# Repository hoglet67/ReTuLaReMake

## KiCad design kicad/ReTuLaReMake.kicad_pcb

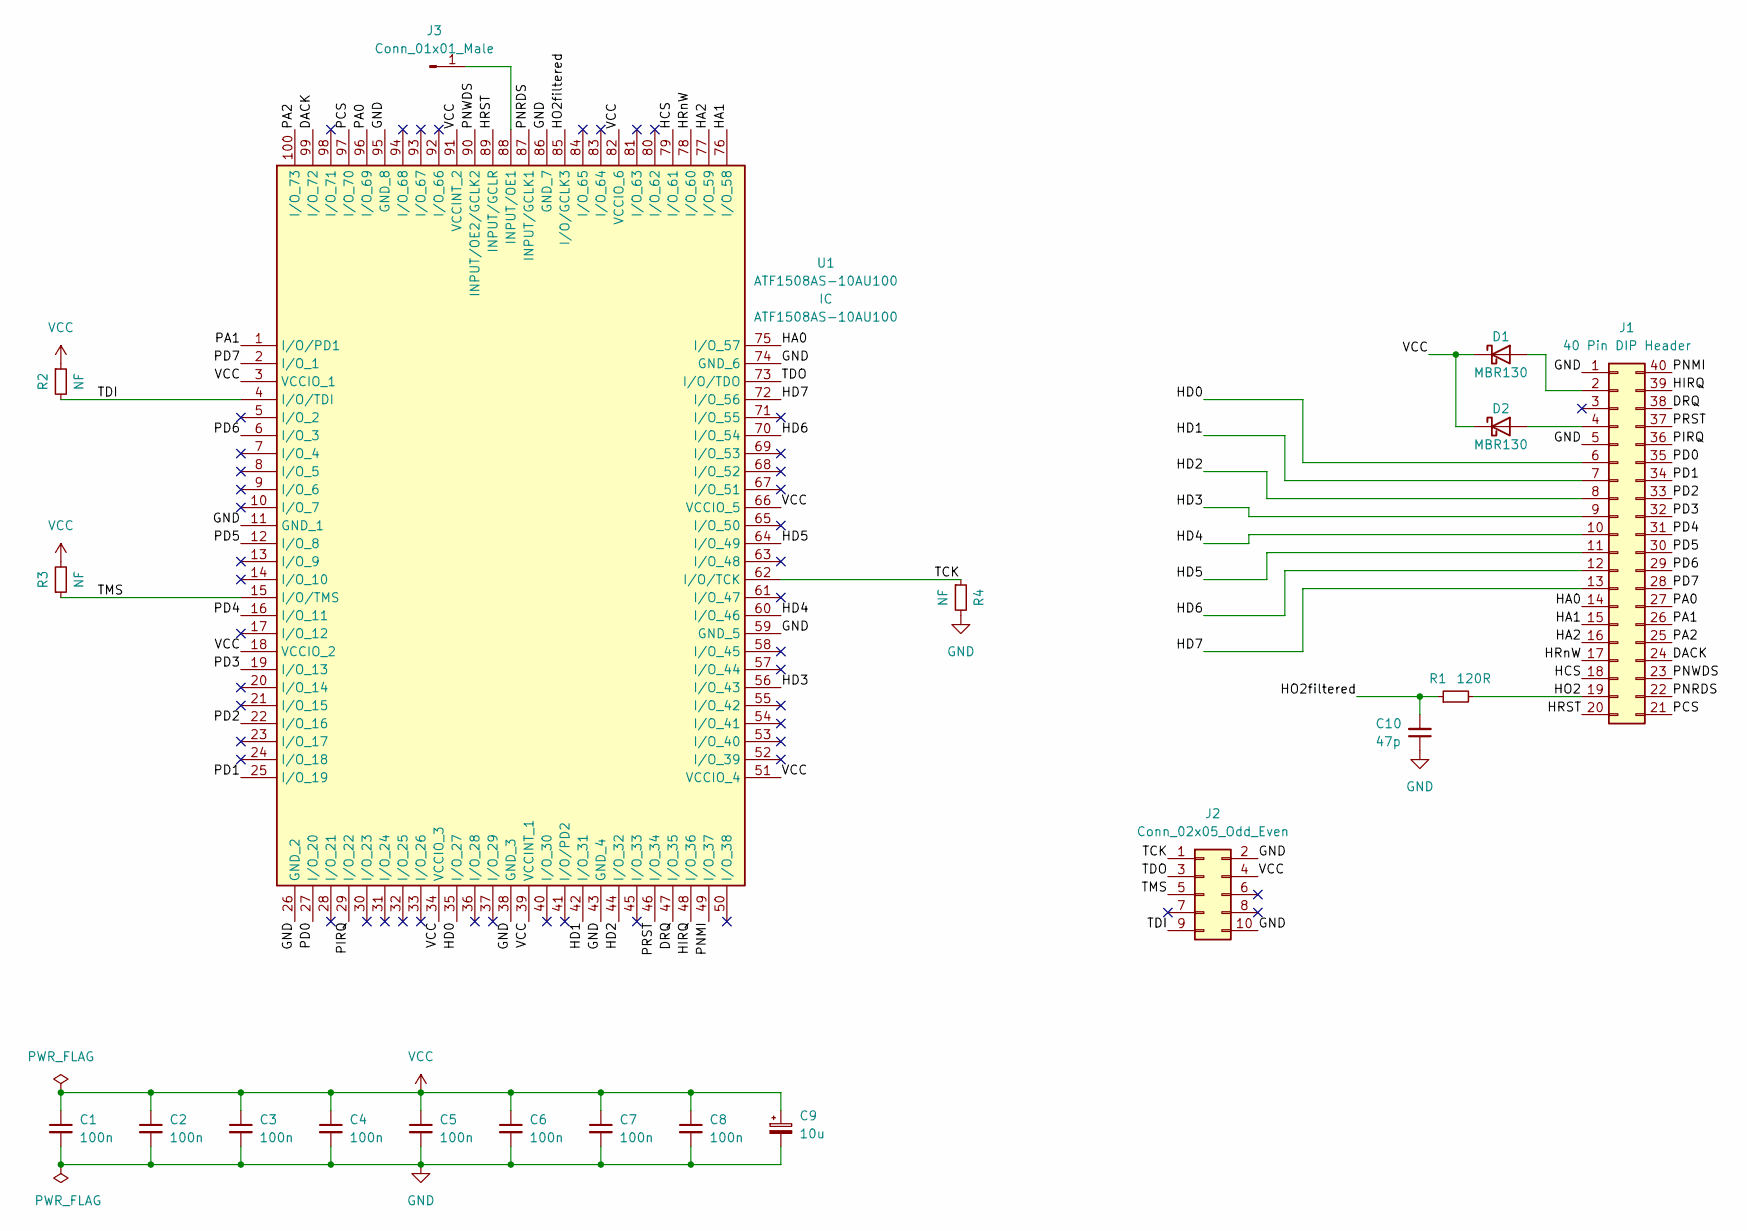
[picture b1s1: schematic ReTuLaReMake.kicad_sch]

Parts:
C1, C2, C3, C4, C5, C6, C7, C8: 100n; C_0805_2012Metric_Pad1.18x1.45mm_HandSolder
C9: 10u; CP_EIA-6032-28_Kemet-C_Pad2.25x2.35mm_HandSolder
C10: 47p; C_0805_2012Metric_Pad1.18x1.45mm_HandSolder
D1, D2: MBR130; D_SOD-123
J1: 40 Pin DIP Header; DIP-40_W15.24mm_Header
J2: Conn_02x05_Odd_Even; PinHeader_2x05_P2.54mm_Vertical
J3: Conn_01x01_Male; PinHeader_1x01_P2.54mm_Vertical
R1: 120R; R_0805_2012Metric_Pad1.20x1.40mm_HandSolder
R2, R3, R4: NF; R_0805_2012Metric_Pad1.20x1.40mm_HandSolder
U1: ATF1508AS-10AU100; TQFP-100_14x14mm_P0.5mm; Manufacturer_Part_Number ATF1508AS-10AU100; Mouser Part Number 556-AF1508AS10AU100

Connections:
/DACK: J1.24, U1.99 (I/O_72)
/DRQ: J1.38, U1.47 (I/O_35)
/HA0: J1.14, U1.75 (I/O_57)
/HA1: J1.15, U1.76 (I/O_58)
/HA2: J1.16, U1.77 (I/O_59)
/HCS: J1.18, U1.79 (I/O_61)
/HD0: J1.6, U1.35 (I/O_27)
/HD1: J1.7, U1.42 (I/O_31)
/HD2: J1.8, U1.44 (I/O_32)
/HD3: J1.9, U1.56 (I/O_43)
/HD4: J1.10, U1.60 (I/O_46)
/HD5: J1.11, U1.64 (I/O_49)
/HD6: J1.12, U1.70 (I/O_54)
/HD7: J1.13, U1.72 (I/O_56)
/HIRQ: J1.39, U1.48 (I/O_36)
/HO2: J1.19, R1.2
/HO2filtered: C10.2, R1.1, U1.85 (I/O/GCLK3)
/HRST: J1.20, U1.89 (INPUT/GCLR)
/HRnW: J1.17, U1.78 (I/O_60)
/PA0: J1.27, U1.96 (I/O_69)
/PA1: J1.26, U1.1 (I/O/PD1)
/PA2: J1.25, U1.100 (I/O_73)
/PCS: J1.21, U1.97 (I/O_70)
/PD0: J1.35, U1.27 (I/O_20)
/PD1: J1.34, U1.25 (I/O_19)
/PD2: J1.33, U1.22 (I/O_16)
/PD3: J1.32, U1.19 (I/O_13)
/PD4: J1.31, U1.16 (I/O_11)
/PD5: J1.30, U1.12 (I/O_8)
/PD6: J1.29, U1.6 (I/O_3)
/PD7: J1.28, U1.2 (I/O_1)
/PIRQ: J1.36, U1.29 (I/O_22)
/PNMI: J1.40, U1.49 (I/O_37)
/PNRDS: J1.22, U1.87 (INPUT/GCLK1)
/PNWDS: J1.23, U1.90 (INPUT/OE2/GCLK2)
/PRST: J1.37, U1.46 (I/O_34)
/TCK: J2.1, R4.1, U1.62 (I/O/TCK)
/TDI: J2.9, R2.2, U1.4 (I/O/TDI)
/TDO: J2.3, U1.73 (I/O/TDO)
/TMS: J2.5, R3.1, U1.15 (I/O/TMS)
GND: C1.2, C2.2, C3.2, C4.2, C5.2, C6.2, C7.2, C8.2, C9.2, C10.1, J1.1, J1.5, J2.2, J2.10, R4.2, U1.11 (GND_1), U1.26 (GND_2), U1.38 (GND_3), U1.43 (GND_4), U1.59 (GND_5), U1.74 (GND_6), U1.86 (GND_7), U1.95 (GND_8)
unnamed: D1.2 (A), J1.2
unnamed: D2.2 (A), J1.4
unnamed: J3.1, U1.88 (INPUT/OE1)
VCC: C1.1, C2.1, C3.1, C4.1, C5.1, C6.1, C7.1, C8.1, C9.1, D1.1 (K), D2.1 (K), J2.4, R2.1, R3.2, U1.3 (VCCIO_1), U1.18 (VCCIO_2), U1.34 (VCCIO_3), U1.39 (VCCINT_1), U1.51 (VCCIO_4), U1.66 (VCCIO_5), U1.82 (VCCIO_6), U1.91 (VCCINT_2)

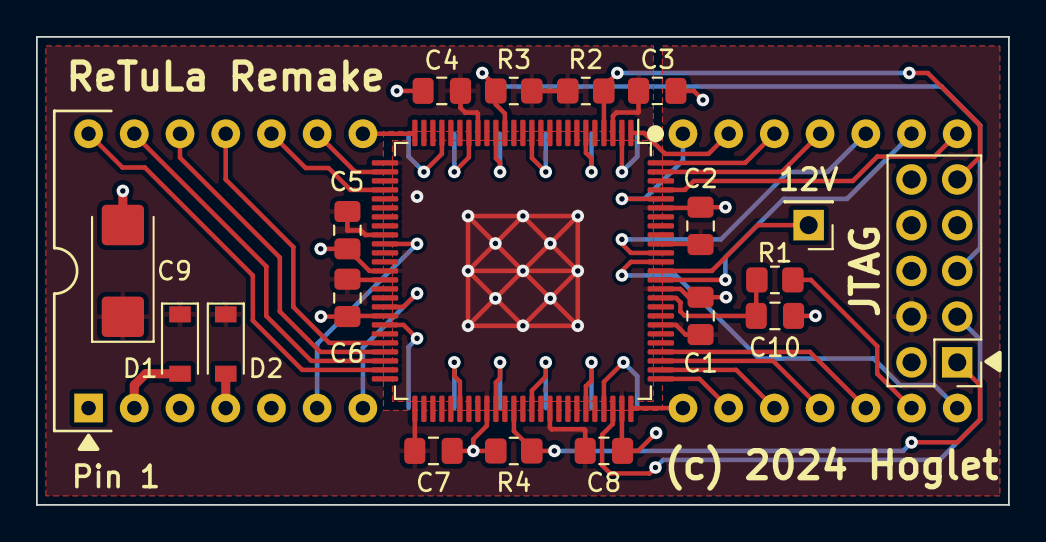
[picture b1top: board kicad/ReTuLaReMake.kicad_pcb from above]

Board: 2 copper layers, 54.0 x 26.0 mm, 20 parts (1 on the bottom side), 45 nets.

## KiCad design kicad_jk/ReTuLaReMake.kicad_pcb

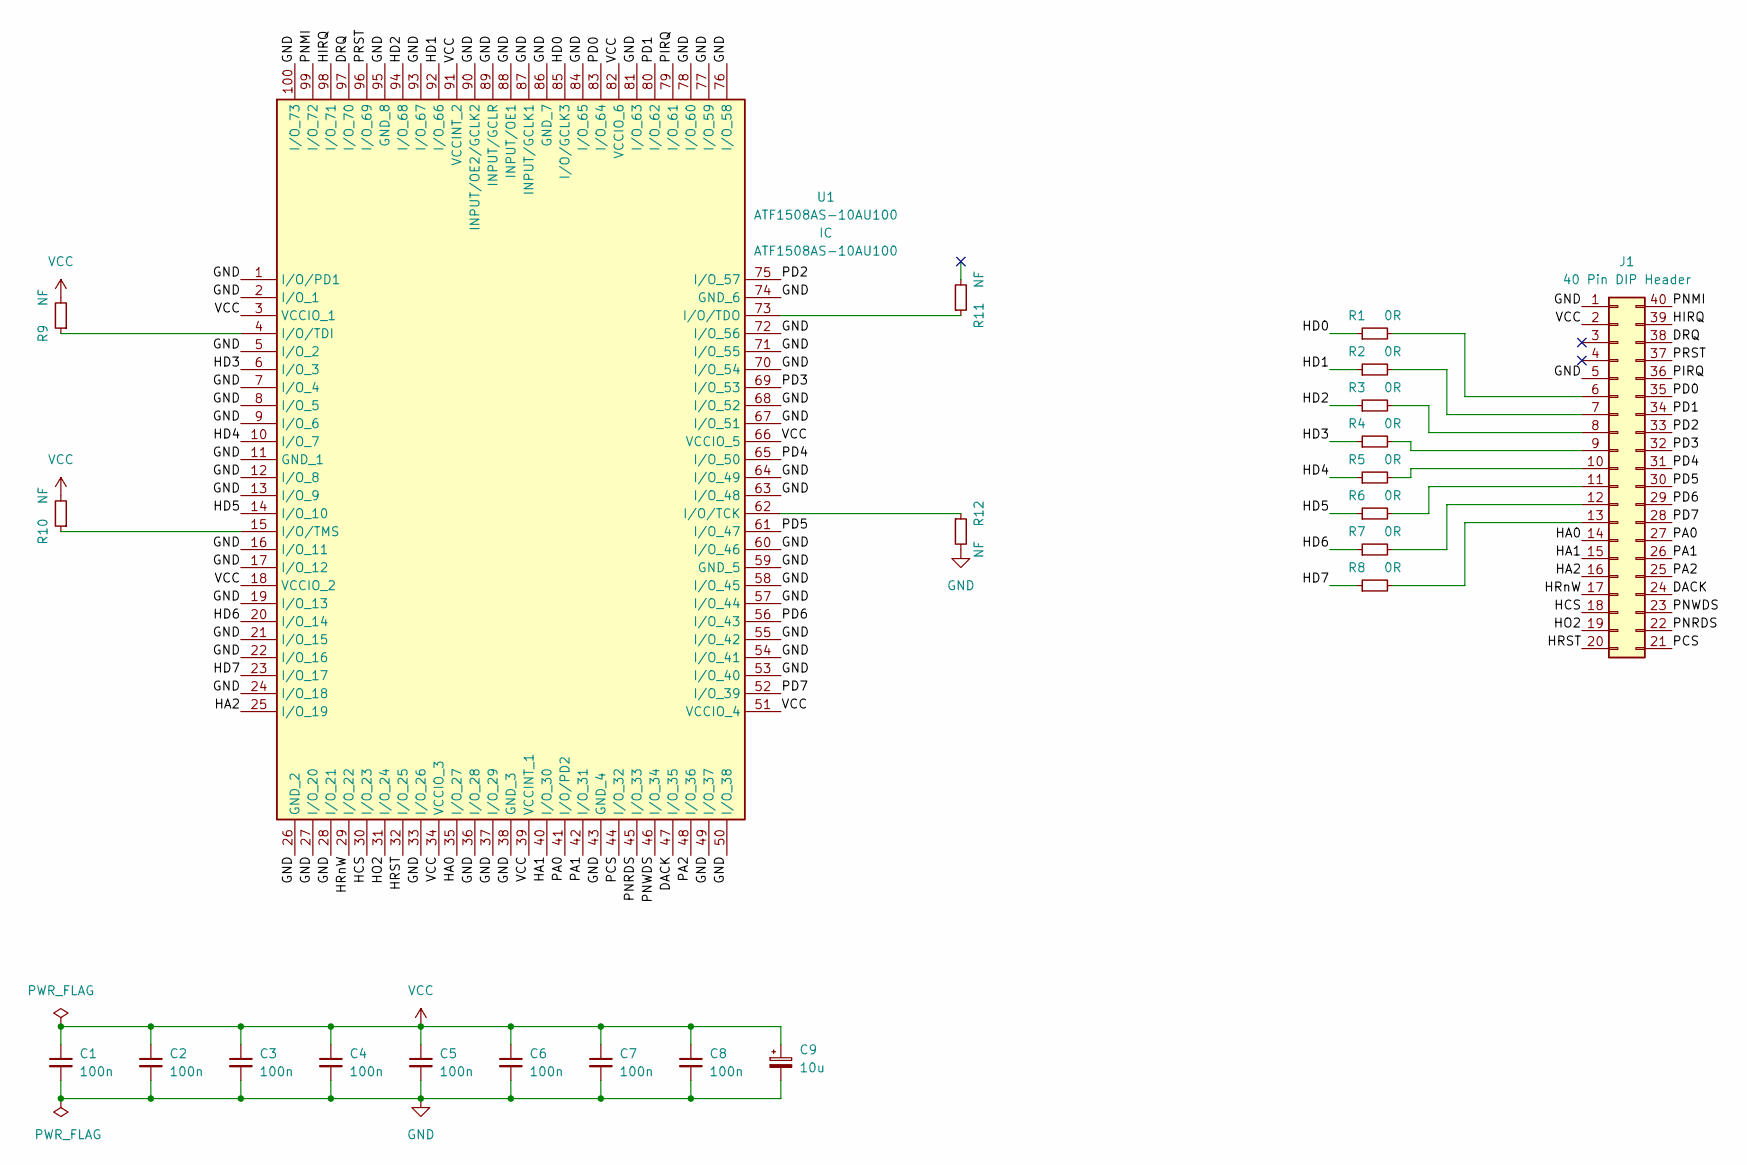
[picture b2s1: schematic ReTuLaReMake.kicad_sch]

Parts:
C1, C2, C3, C4, C5, C6, C7, C8: 100n; C_0805_2012Metric_Pad1.18x1.45mm_HandSolder
C9: 10u; CP_EIA-6032-28_Kemet-C_Pad2.25x2.35mm_HandSolder
J1: 40 Pin DIP Header; DIP-40_W15.24mm_Header
R1, R2, R3, R4, R5, R6, R7, R8: 0R; R_0805_2012Metric_Pad1.20x1.40mm_HandSolder
R9, R10, R11, R12: NF; R_1206_3216Metric
U1: ATF1508AS-10AU100; TQFP-100_14x14mm_P0.5mm; Manufacturer_Part_Number ATF1508AS-10AU100; Mouser Part Number 556-AF1508AS10AU100

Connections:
/DACK: J1.24, U1.47 (I/O_35)
/DRQ: J1.38, U1.97 (I/O_70)
/HA0: J1.14, U1.35 (I/O_27)
/HA1: J1.15, U1.40 (I/O_30)
/HA2: J1.16, U1.25 (I/O_19)
/HCS: J1.18, U1.30 (I/O_23)
/HD0: R1.1, U1.85 (I/O/GCLK3)
/HD1: R2.1, U1.92 (I/O_66)
/HD2: R3.1, U1.94 (I/O_68)
/HD3: R4.1, U1.6 (I/O_3)
/HD4: R5.1, U1.10 (I/O_7)
/HD5: R6.1, U1.14 (I/O_10)
/HD6: R7.1, U1.20 (I/O_14)
/HD7: R8.1, U1.23 (I/O_17)
/HIRQ: J1.39, U1.98 (I/O_71)
/HO2: J1.19, U1.31 (I/O_24)
/HRST: J1.20, U1.32 (I/O_25)
/HRnW: J1.17, U1.29 (I/O_22)
/PA0: J1.27, U1.41 (I/O/PD2)
/PA1: J1.26, U1.42 (I/O_31)
/PA2: J1.25, U1.48 (I/O_36)
/PCS: J1.21, U1.44 (I/O_32)
/PD0: J1.35, U1.83 (I/O_64)
/PD1: J1.34, U1.80 (I/O_62)
/PD2: J1.33, U1.75 (I/O_57)
/PD3: J1.32, U1.69 (I/O_53)
/PD4: J1.31, U1.65 (I/O_50)
/PD5: J1.30, U1.61 (I/O_47)
/PD6: J1.29, U1.56 (I/O_43)
/PD7: J1.28, U1.52 (I/O_39)
/PIRQ: J1.36, U1.79 (I/O_61)
/PNMI: J1.40, U1.99 (I/O_72)
/PNRDS: J1.22, U1.45 (I/O_33)
/PNWDS: J1.23, U1.46 (I/O_34)
/PRST: J1.37, U1.96 (I/O_69)
GND: C1.2, C2.2, C3.2, C4.2, C5.2, C6.2, C7.2, C8.2, C9.2, J1.1, J1.5, R12.2, U1.1 (I/O/PD1), U1.2 (I/O_1), U1.5 (I/O_2), U1.7 (I/O_4), U1.8 (I/O_5), U1.9 (I/O_6), U1.11 (GND_1), U1.12 (I/O_8), U1.13 (I/O_9), U1.16 (I/O_11), U1.17 (I/O_12), U1.19 (I/O_13), U1.21 (I/O_15), U1.22 (I/O_16), U1.24 (I/O_18), U1.26 (GND_2), U1.27 (I/O_20), U1.28 (I/O_21), U1.33 (I/O_26), U1.36 (I/O_28), U1.37 (I/O_29), U1.38 (GND_3), U1.43 (GND_4), U1.49 (I/O_37), U1.50 (I/O_38), U1.53 (I/O_40), U1.54 (I/O_41), U1.55 (I/O_42), U1.57 (I/O_44), U1.58 (I/O_45), U1.59 (GND_5), U1.60 (I/O_46), U1.63 (I/O_48), U1.64 (I/O_49), U1.67 (I/O_51), U1.68 (I/O_52), U1.70 (I/O_54), U1.71 (I/O_55), U1.72 (I/O_56), U1.74 (GND_6), U1.76 (I/O_58), U1.77 (I/O_59), U1.78 (I/O_60), U1.81 (I/O_63), U1.84 (I/O_65), U1.86 (GND_7), U1.87 (INPUT/GCLK1), U1.88 (INPUT/OE1), U1.89 (INPUT/GCLR), U1.90 (INPUT/OE2/GCLK2), U1.93 (I/O_67), U1.95 (GND_8), U1.100 (I/O_73)
unnamed: J1.6, R1.2
unnamed: J1.7, R2.2
unnamed: J1.8, R3.2
unnamed: J1.9, R4.2
unnamed: J1.10, R5.2
unnamed: J1.11, R6.2
unnamed: J1.12, R7.2
unnamed: J1.13, R8.2
unnamed: R9.1, U1.4 (I/O/TDI)
unnamed: R10.1, U1.15 (I/O/TMS)
unnamed: R11.1, U1.73 (I/O/TDO)
unnamed: R12.1, U1.62 (I/O/TCK)
VCC: C1.1, C2.1, C3.1, C4.1, C5.1, C6.1, C7.1, C8.1, C9.1, J1.2, R9.2, R10.2, U1.3 (VCCIO_1), U1.18 (VCCIO_2), U1.34 (VCCIO_3), U1.39 (VCCINT_1), U1.51 (VCCIO_4), U1.66 (VCCIO_5), U1.82 (VCCIO_6), U1.91 (VCCINT_2)

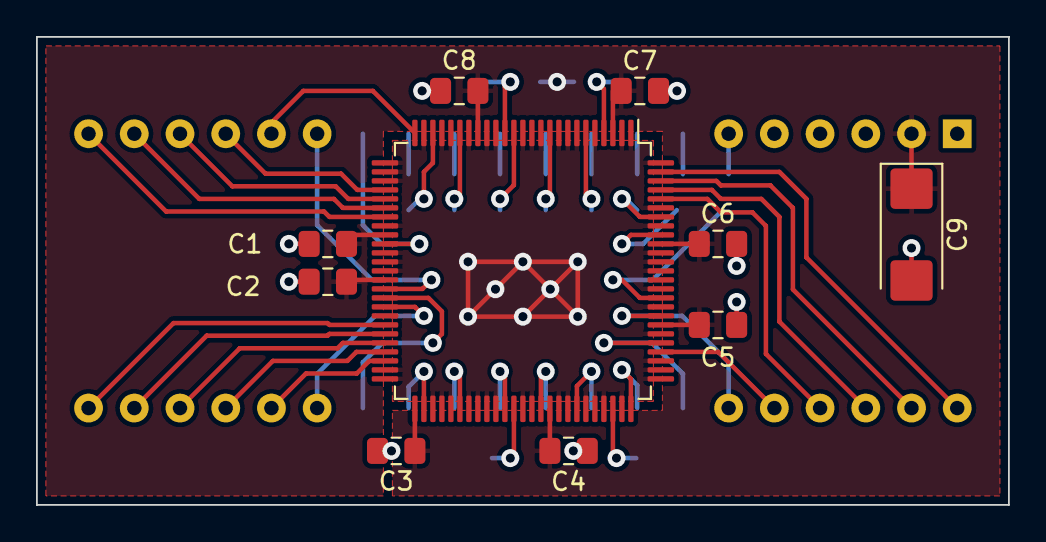
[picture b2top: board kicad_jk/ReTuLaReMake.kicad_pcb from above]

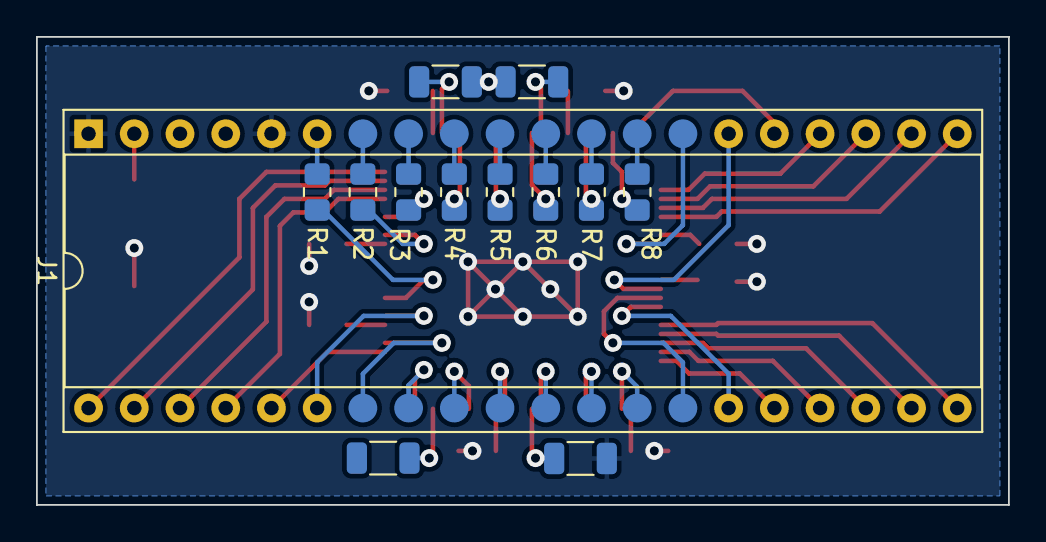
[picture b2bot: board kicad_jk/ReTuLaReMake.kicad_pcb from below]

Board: 2 copper layers, 54.0 x 26.0 mm, 23 parts (13 on the bottom side), 49 nets.

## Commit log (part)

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2023-11-27 Initial version
2023-11-27 KiCAD: Move PA0
2023-11-27 KiCAD: Board settings
2023-11-27 KiCAD: Make VIAs 1.0mm/0.5mm
2023-11-28 KiCAD: Move HD1/0 to valid pins
2023-11-28 CPLD: Initial version
2023-11-28 CPLD: re-code flags structurally
2023-11-29 Seperate altera and xilinx builds
2023-11-29 CPLD: fix bug with nmi flag
2023-12-02 CPLD: refactor, no logic changes, same resource usage
2023-12-04 CPLD: Factor out R3 and try a two-byte impl
2023-12-04 CPLD: Try replacing rs_latch with ar_dff
2023-12-05 CPLD: Refactored and added implementation choices
2023-12-05 CPLD: Seperate Xilinx FPGA and CPLD builds
2023-12-05 CPLD: Fix typos
2023-12-07 CPLD: Fix bug in one-byte R3
2023-12-07 CPLD: Add more efficient R124 flag impl for Xilinx CPLDs
2023-12-08 CPLD: Minimal version using XC9572XL
2023-12-09 CPLD: Add Atmel tools
2023-12-09 CPLD: Start CUPL version (euch)
2023-12-09 CPLD: Add parasite power detection
2023-12-09 KiCAD: Correct pin assignments to match JK's PCBs
2023-12-09 KiCAD: Connect unused CPLD pins to GND
2023-12-09 CPLD: Refresh Altera pinout to match JK's PCBs
2023-12-09 CPLD: Refresh CUPL pinout to match JK's PCBs
2023-12-09 CPLD: CUPL, refactor to avoid CK CE conflict
2023-12-09 CPLD: Verilog, added pin assignment for aft15xx_yosys flow
2023-12-09 CPLD: CUPL, encode multiplexers using sets
2023-12-11 CPLD: yosys flow, correct fixed pinout
2023-12-11 CPLD: CUPL, tweak build options so design fits
2023-12-11 CPLD: CUPL, fix bug in SAV assignments
2023-12-11 CPLD: CUPL, re-order (cosmetic, same equations)
2023-12-12 KiCAD: Take snapshot of design with JK's pin allocation
2023-12-12 KiCAD: Rotated CPLD 180 degrees and changed pinout
2023-12-12 CPLD: yosys flow, update pinout
2024-01-07 CPLD: Verilog, implement p_powered_off using OE
2024-01-07 CPLD: CUPL, add parasite power detection
2024-01-07 CPLD: CUPL, Use CE for Control registers
2024-01-07 CPLD: Add XC9572XL define to xilinx project
2024-01-07 CPLD: CUPL, fix a typo in p_data OE
2024-01-07 CPLD: CUPL, make h_irq_b optional
2024-01-07 CPLD: CUPL, implement two-byte mode (doesn't quite fit)
2024-01-07 CPLD: CUPL, update pinout
2024-01-07 CPLD: CUPL, add global_oe option
2024-01-07 CPLD: CUPL, use CE for FIFO registers
2024-01-07 CPLD: CUPL, add exclusive impl for HP1/2/4 and PH1/2/4
2024-01-07 KiCad: Move p_rd_b to a global clock
2024-01-07 CPLD: CUPL, Move p_rd_b to a global clock
2024-01-07 CPLD: Altera, switch to Atmel pinout
2024-01-07 CPLD: Yosys, Move p_rd_b to a global clock
2024-01-07 KiCAD: Added JTAG Connector
2024-01-08 CPLD: CUPL, Move p_data2/1/0 and disable xor synthesis
2024-01-08 KiCAD: Update pins for p_data2/1/0
2024-01-08 CPLD: CUPL, factor out reset term (cosmetic)
2024-01-08 CPLD: CUPL, Use -m0 in wincupl
2024-01-08 CPLD: CUPL, Make nmi_flag a pin node to reduce block fan-in
2024-01-08 CPLD: CUPL, Fix mistake in p_rst_b term
2024-01-08 CPLD: CUPL, use pinnode= instead of node
2024-01-08 CPLD: CUPL, save 4 pts
2024-01-08 CPLD: CUPL, Update properties
2024-01-08 KiCAD: Add schottky diodes
2024-01-08 KiCAD: Add 12V OE1 Test Point
2024-01-08 KiCAD: Remove GNDs on unused I/Os
2024-01-08 CPLD: CUPL, make h_irq_b open collector
2024-01-08 CPLD: CUPL, try enabling h_irq_b (doesn't fit)
2024-01-08 .gitignore only
2024-01-08 CPLD: CUPL, p_powered_off uses global OE
2024-01-08 CPLD: CUPL, make reset pinout to reduce block fan-in significantly
2024-01-09 CPLD: CUPL, fix some bugs found in simulation
2024-01-09 CPLD: CUPL, check in simulation
2024-01-17 CPLD: CUPL, improve simulation
2024-01-18 KiCAD: Add clock filter; adjust decoupling
2024-01-18 KiCAD: Update header to have four more thru-hole pins
2024-01-18 KiCAD: Improve C7/8 routing
2024-01-18 KiCAD: Improve C5/6 routing
2024-01-18 KiCAD: Check then add manufacturing files
2024-01-19 CPLD: CUPL, add drq = nmi_flag
2024-01-19 KiCAD: Add JLCJLCJLCJLC
2024-01-19 KiCAD: Shrink vias to 0.4mm/0.8mm
2024-01-19 KiCAD: Move vias off pads
2024-01-31 CPLD: CUPL, enable pin keeper
2024-02-02 CPLD: CUPL, update build scripts to created svf file for programming
2024-02-02 CPLD: CUPL, use reduced power mode on macrocells
2024-02-02 CPLD: CUPL, correct behaviour of PH1/PH3/HP3 when full
2024-02-03 KiCAD: Rotate board so text the right way up
2024-02-03 KiCAD: Remove R1-R8
2024-02-03 KiCAD: Reduce via size to 0.7/0.3mm, add more GND vias
2024-02-03 KiCAD: Move clock filter to top side
2024-02-03 KiCAD: Move R2/3/4 to top side

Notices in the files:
kicad/ReTuLaReMake.kicad_pcb:
(c) 2024 Hoglet
